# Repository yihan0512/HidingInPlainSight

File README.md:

# This is the code for our Usenix security 2022 paper "Hiding in Plain Sight? On the Efficacy of Power Side Channel-Based Control Flow Monitoring"

## Our paper can be found here.

## installation
- install anaconda3
- create a conda virtual environment: `conda create --prefix ./environment python=3.8`
- install pytorch: follow instructions on pytorch.org to install the pytorch version that fits your cuda version
- install hmmlearn: `pip install hmmlearn`
- install our customized chipwhisperer (in `chipwhisperer/`): `python -m pip install -e . --user`

## how to use
please check the readme file in each subdirectory for detailed steps for each program

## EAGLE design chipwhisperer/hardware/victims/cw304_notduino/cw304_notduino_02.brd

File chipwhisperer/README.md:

# ChipWhisperer

[Wiki](https://wiki.newae.com/V5:Main_Page) |[Documentation](https://chipwhisperer.readthedocs.io) |[Knowledge Base](https://wiki.newae.com/Category:Knowledge_Base) | [Forum](http://www.newae.com/forum) | [Store](https://store.newae.com) | [NewAE](http://newae.com)

ChipWhisperer is an open source toolchain dedicated to hardware security research. This toolchain consists of several layers of open source components:
* __Hardware__: The ChipWhisperer uses a _capture_ board and a _target_ board. Schematics and PCB layouts for the ChipWhisperer-Lite capture board and a number of target boards are freely available.
* __Firmware__: Three separate pieces of firmware are used on the ChipWhisperer hardware. The capture board has a USB controller (in C) and an FPGA for high-speed captures (in Verilog) with open-source firmware. Also, the target device has its own firmware; this repository includes many firmware examples for different targets.
* __Software__: The ChipWhisperer software is made up of a _capture_ program to control the hardware and an _analyzer_ program to process captured data.

---

## ChipWhisperer 5.0 Is Here

The biggest (and most breaking) change is here. ChipWhisperer 5.0 uses Python 3 & Juypter Notebooks. Here is a brief summary of improvements:

* Uses Jupyter Notebooks
* Python 3 
* Fully documented API (finally)
* 19 Jupyter notebook tutorials for side-channel analysis with ChipWhisperer
* 5x improved capture speed
* Tutorials all include output with three different targets (Nano, Lite (XMEGA), Lite (STM32F)), making it easier to compare your output to the tutorials output when you are following along.
* Fully usable as a standalone python package
* Project API supports import and export to zip file to move projects around.

An overview of the major changes can be found on the new ReadtheDocs [Overview Page](https://chipwhisperer.readthedocs.io/en/stable/getting-started.html).

We highly recommend you switch to CW5 as all development since last year has been for CW5, and will continue this way. The final tagged version of CW4 is 4.0.5, it can be found in the **develop** branch if you insist. 

## Getting Started
First time using ChipWhisperer? Check out these links:
* [Getting Started](https://wiki.newae.com/V5:Getting_Started) if you have no idea where to start
* [CW5 Information](https://wiki.newae.com/CW5) for information about ChipWhisperer 5 and Jupyter.
* [Installing ChipWhisperer](https://chipwhisperer.readthedocs.io/en/latest/installing.html) if you're trying to set up this software package

## GIT Source
Note all development occurs on the [develop](https://github.com/newaetech/chipwhisperer/tree/develop) branch. If you are looking for bleeding edge it's NOT on master - we push each release (and possibly any critical changes) to master. This means that "master" always gives you the latest known-working branch, but there may be new features on the "develop" branch.

## Help!
Stuck? If you need a hand, there are a few places you can ask for help:
* The [NewAE Forum](https://www.newae.com/forum/) is full of helpful people that can point you in the right direction
* If you find a bug, let us know through the [issue tracker](https://github.com/newaetech/chipwhisperer/issues)

---

ChipWhisperer is a trademark of NewAE Technology Inc., registered in the US, Europe, and China.

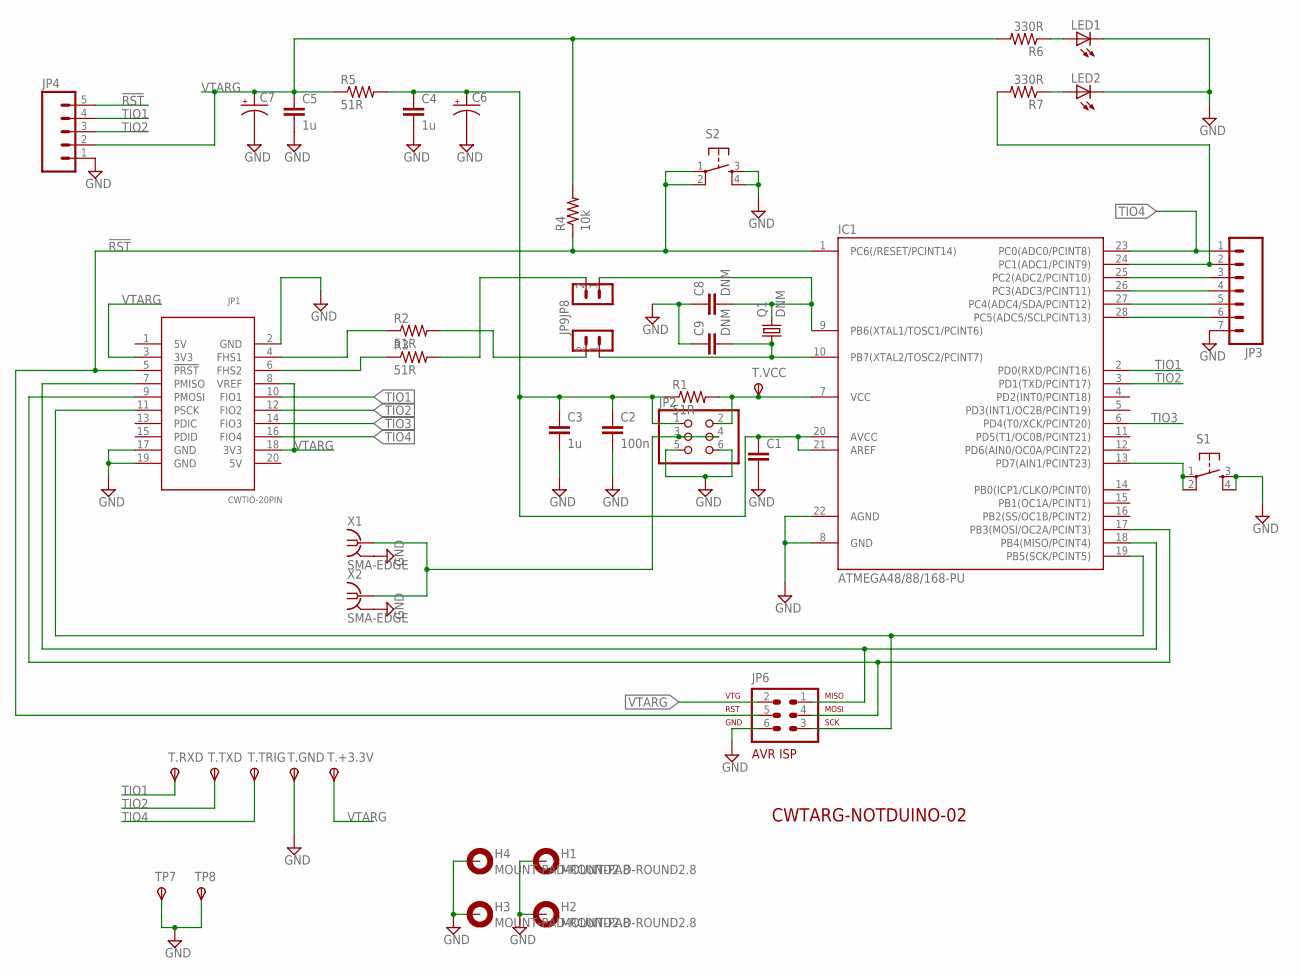
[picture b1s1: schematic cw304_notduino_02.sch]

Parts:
C1: CAPPTH; CAP-PTH-SMALL
C2: 100n; CAP-PTH-SMALL
C3, C4, C5: 1u; CAP-PTH-SMALL
C6, C7: CAP_POLPTH1; CPOL-RADIAL-100UF-25V
C8, C9: DNM; CAP-PTH-SMALL
H1, H2, H3, H4: MOUNT-PAD-ROUND2.8; 2,8-PAD
IC1: ATMEGA48/88/168-PU; DIL28-3
JP1: CWTIO-20PIN; PINSHRD_PTH_2X10
JP2: PINHD-2X3; 2X03
JP3: M07LOCK; 1X07_LOCK
JP4: M05LOCK; 1X05_LOCK
JP6: AVR-ISP-6
JP8, JP9: M02LOCK; 1X02_LOCK
LED1, LED2: LED5MM
Q1: DNM; HC49U-V
R1, R2, R3, R5: 51R; AXIAL-0.4
R4: 10k; AXIAL-0.4
R6, R7: 330R; AXIAL-0.4
S1, S2: TAC_SWITCHPTH; TACTILE-PTH
T.+3.3V, T.GND, T.RXD, T.TRIG, T.TXD: TPSPAD1-13; P1-13
T.VCC: TPSPAD1-17; P1-17
TP7, TP8: TPSPAD1-17; P1-17
X1, X2: SMA-EDGE; J502-ND-142-0711-821/826

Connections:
!RST: IC1.1 (PC6(/RESET/PCINT14)), JP1.5 (!PRST), JP4.5, JP6.5, R4.P$1 (1), S2.1, S2.2
GND: C1.2, C2.2, C3.2, C4.2, C5.2, C6.2 (-), C7.2 (-), C8.1, C9.1, H1.B2,8, H2.B2,8, H3.B2,8, H4.B2,8, IC1.8 (GND), IC1.22 (AGND), JP1.2 (GND), JP1.17 (GND), JP1.19 (GND), JP2.5, JP2.6, JP3.7, JP4.1, JP6.6, LED1.K (C), LED2.K (C), S1.3, S1.4, S2.3, S2.4, T.GND.TP, TP7.TP, TP8.TP, X1.G@1 (2), X1.G@2 (2), X1.G@3 (2), X1.G@4 (2), X2.G@1 (2), X2.G@2 (2), X2.G@3 (2), X2.G@4 (2)
unnamed: LED2.A, R7.P$1 (1)
unnamed: IC1.18 (PB4(MISO/PCINT4)), JP1.7 (PMISO), JP6.1
unnamed: IC1.17 (PB3(MOSI/OC2A/PCINT3)), JP1.9 (PMOSI), JP6.4
unnamed: JP1.4 (FHS1), R2.P$1 (1)
unnamed: JP1.6 (FHS2), R3.P$1 (1)
unnamed: IC1.19 (PB5(SCK/PCINT5)), JP1.11 (PSCK), JP6.3
unnamed: IC1.7 (VCC), JP2.2, R1.P$2 (2), T.VCC.TP
unnamed: LED1.A, R6.P$1 (1)
unnamed: C1.1, C2.1, C3.1, C4.1, C6.1 (+), IC1.20 (AVCC), IC1.21 (AREF), JP2.1, R1.P$1 (1), R5.P$2 (2)
unnamed: C8.2, IC1.9 (PB6(XTAL1/TOSC1/PCINT6)), JP8.1, Q1.2
unnamed: IC1.13 (PD7(AIN1/PCINT23)), S1.1, S1.2
unnamed: IC1.24 (PC1(ADC1/PCINT9)), JP3.2, R7.P$2 (2)
unnamed: IC1.25 (PC2(ADC2/PCINT10)), JP3.3
unnamed: IC1.26 (PC3(ADC3/PCINT11)), JP3.4
unnamed: IC1.27 (PC4(ADC4/SDA/PCINT12)), JP3.5
unnamed: IC1.28 (PC5(ADC5/SCLPCINT13)), JP3.6
unnamed: JP2.3, JP2.4, X1.1, X2.1
unnamed: C9.2, IC1.10 (PB7(XTAL2/TOSC2/PCINT7)), JP9.1, Q1.1
THS1: JP9.2, R2.P$2 (2)
THS2: JP8.2, R3.P$2 (2)
TIO1: IC1.2 (PD0(RXD/PCINT16)), JP1.10 (FIO1), JP4.4, T.RXD.TP
TIO2: IC1.3 (PD1(TXD/PCINT17)), JP1.12 (FIO2), JP4.3, T.TXD.TP
TIO3: IC1.6 (PD4(T0/XCK/PCINT20)), JP1.14 (FIO3)
TIO4: IC1.23 (PC0(ADC0/PCINT8)), JP1.16 (FIO4), JP3.1, T.TRIG.TP
VTARG: C5.1, C7.1 (+), JP1.3 (3V3), JP1.8 (VREF), JP1.18 (3V3), JP4.2, JP6.2, R4.P$2 (2), R5.P$1 (1), R6.P$2 (2), T.+3.3V.TP

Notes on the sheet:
CWTARG-NOTDUINO-02

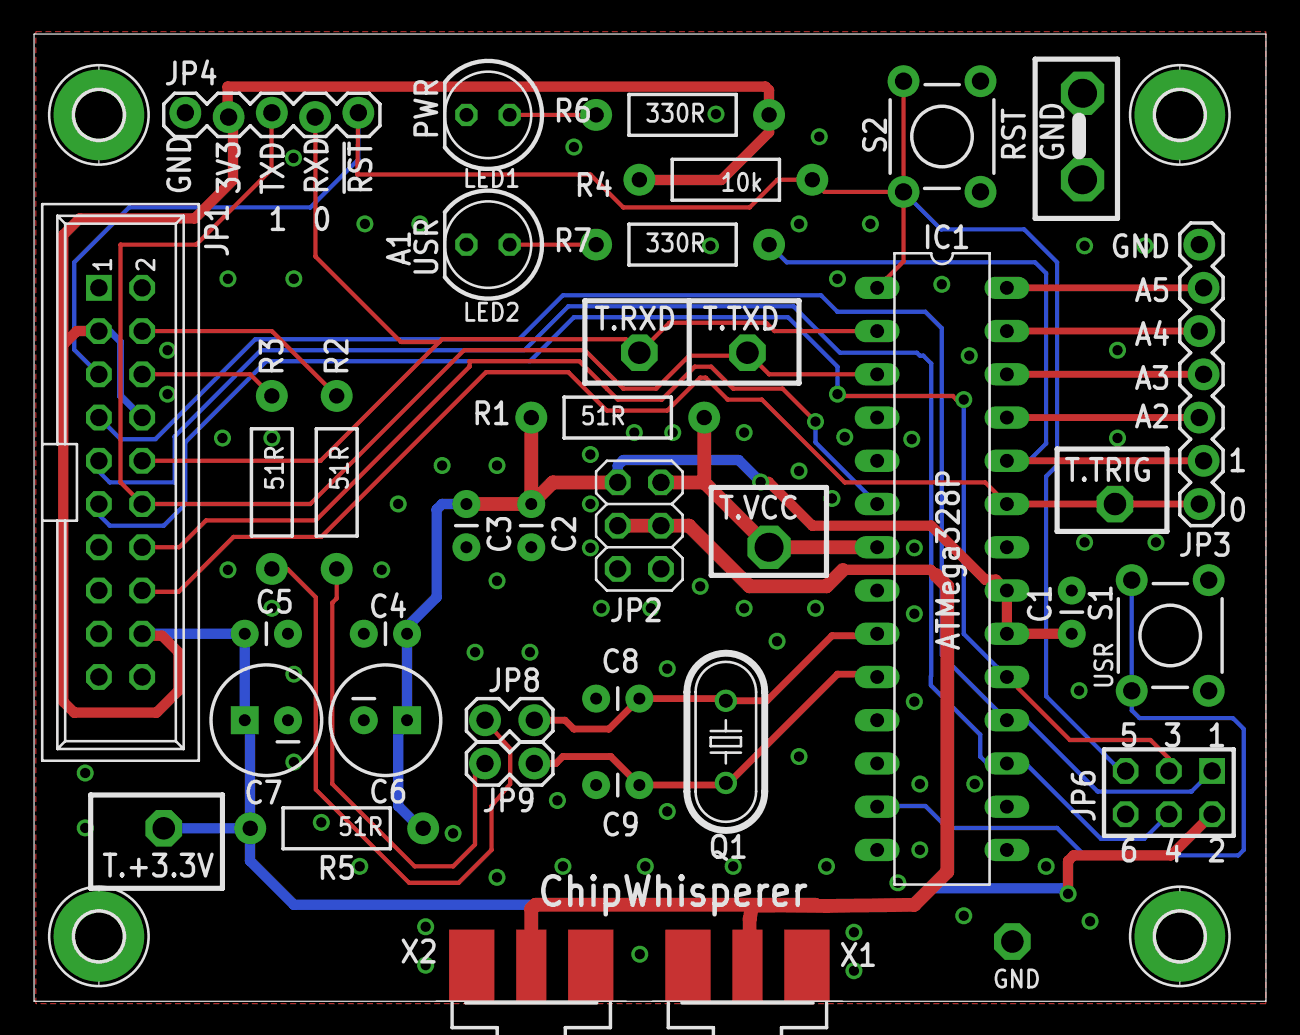
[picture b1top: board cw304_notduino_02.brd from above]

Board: 2 copper layers, 72.4 x 56.8 mm, 43 parts (0 on the bottom side), 27 nets.

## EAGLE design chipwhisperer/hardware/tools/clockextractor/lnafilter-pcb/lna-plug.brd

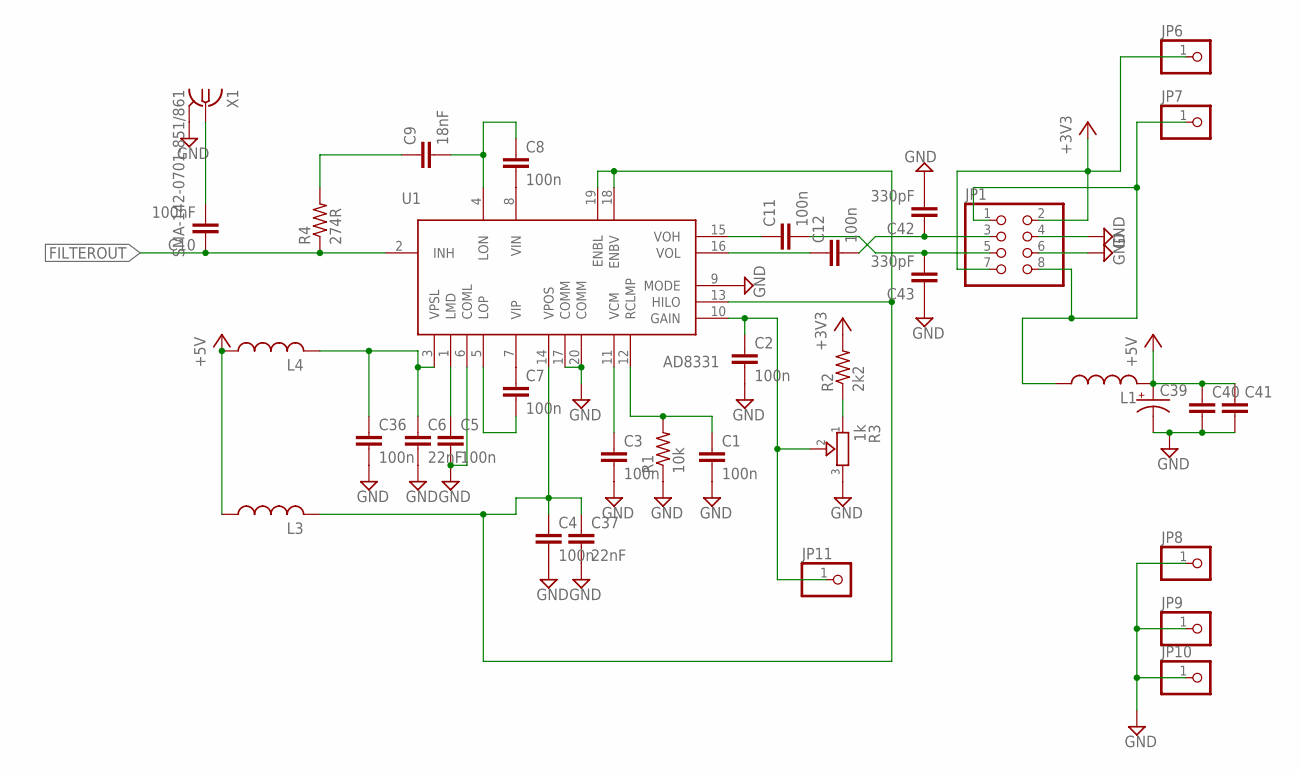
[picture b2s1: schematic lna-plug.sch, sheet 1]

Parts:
C1, C2, C3, C4, C5, C7, C8, C11, C12, C36: 100n; C0603
C6, C37: 22nF; C0603
C9: 18nF; C0603
C10: 100nF; C0603
C39: CPOL-USSMCC; SMC_C
C40: C-EUC1206; C1206
C41: C-EUC0805; C0805
C42, C43: 330pF; C0603
JP1: PINHD-2X4; 2X04
JP6, JP7, JP8, JP9, JP10, JP11: PINHD-1X1; 1X01
L1, L3, L4: L-USL2012C; L2012C
R1: 10k; R0603
R2: 2k2; R0603
R3: 1k; TRIMMER_3362P
R4: 274R; R0603
U1: AD8331; QSOP20
X1: SMA-142-0701-851/861; J502-ND-142-0701-851/861

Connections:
+3V3: JP1.2, JP1.7, JP6.1, R2.2; also elsewhere on the board
+5V: C39.+, C40.1, C41.1, L1.2, L3.1, L4.1
FILTEROUT: C10.1, R4.1, U1.2 (INH); also elsewhere on the board
GND: C1.2, C2.2, C3.2, C4.2, C5.2, C6.2, C36.2, C37.2, C39.-, C40.2, C41.2, C42.2, C43.1, JP1.4, JP1.6, JP8.1, JP9.1, JP10.1, R1.1, R3.3, U1.6 (COML), U1.9 (MODE), U1.17 (COMM), U1.20 (COMM), X1.G@1 (2), X1.G@2 (2), X1.G@3 (2), X1.G@4 (2); also elsewhere on the board
unnamed: C7.1, U1.7 (VIP)
unnamed: C8.2, U1.8 (VIN)
unnamed: C8.1, C9.2, U1.4 (LON)
unnamed: C7.2, U1.5 (LOP)
unnamed: C3.1, U1.11 (VCM)
unnamed: C1.1, R1.2, U1.12 (RCLMP)
unnamed: C2.1, JP11.1, R3.2, U1.10 (GAIN)
unnamed: R2.1, R3.1
unnamed: C5.1, U1.1 (LMD)
unnamed: C6.1, C36.1, L4.2, U1.3 (VPSL)
unnamed: C9.1, R4.2
unnamed: C12.1, U1.16 (VOL)
unnamed: C11.1, U1.15 (VOH)
unnamed: C12.2, C42.1, JP1.3
unnamed: C11.2, C43.2, JP1.5
unnamed: JP1.1, JP1.8, JP7.1, L1.1
unnamed: C10.2, X1.1
unnamed: C4.1, C37.1, L3.2, U1.13 (HILO), U1.14 (VPOS), U1.18 (ENBV), U1.19 (ENBL)

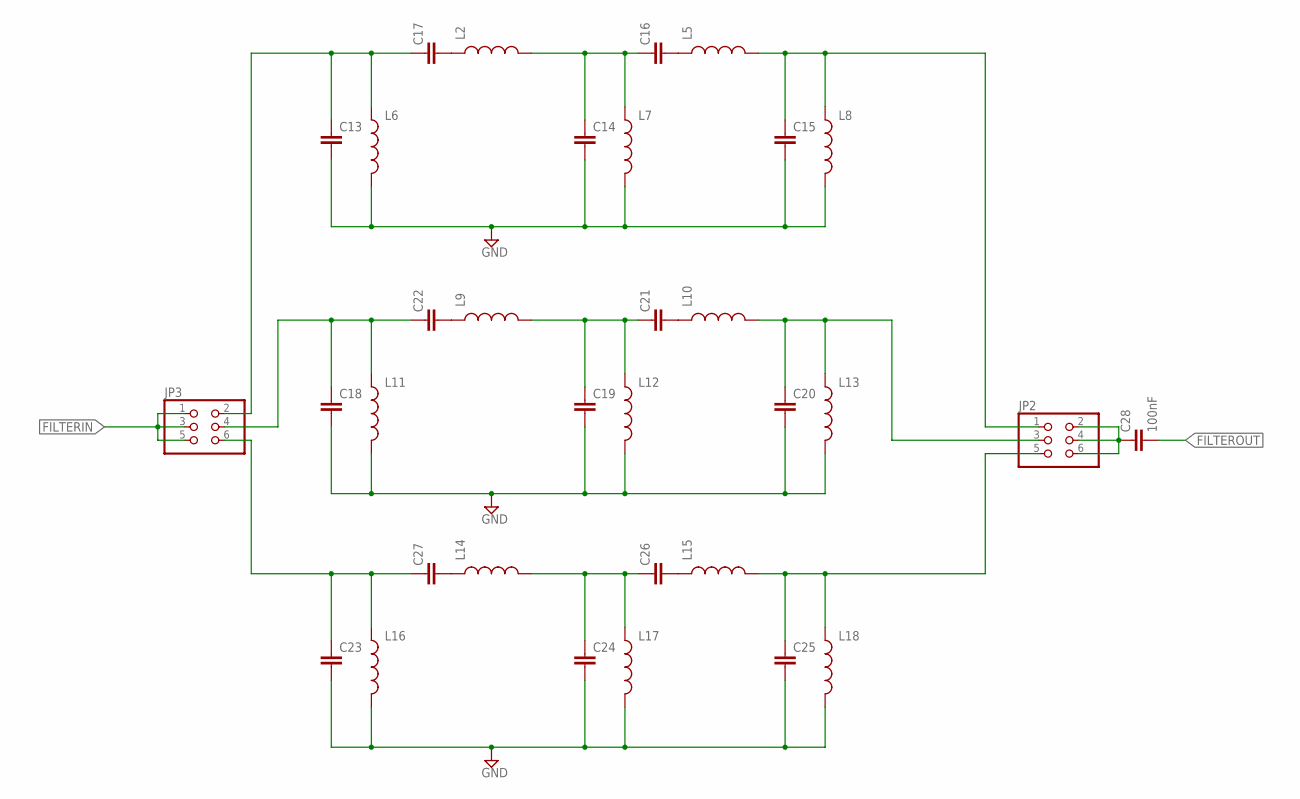
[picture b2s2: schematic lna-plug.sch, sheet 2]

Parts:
C13, C14, C15, C16, C17, C18, C19, C20, C21, C22, C23, C24, C25, C26, C27: C-EUC0603; C0603
C28: 100nF; C0603
JP2, JP3: PINHD-2X3; 2X03
L2, L5, L6, L7, L8, L9, L10, L11, L12, L13, L14, L15, L16, L17, L18: INDUCTOR0603; 0603

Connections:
FILTERIN: JP3.1, JP3.3, JP3.5; also elsewhere on the board
FILTEROUT: C28.2; also elsewhere on the board
GND: C13.2, C14.2, C15.2, C18.2, C19.2, C20.2, C23.2, C24.2, C25.2, L6.2, L7.2, L8.2, L11.2, L12.2, L13.2, L16.2, L17.2, L18.2; also elsewhere on the board
unnamed: C17.2, L2.1
unnamed: C16.2, L5.1
unnamed: C14.1, C16.1, L2.2, L7.1
unnamed: C15.1, JP2.1, L5.2, L8.1
unnamed: C23.1, C27.1, JP3.6, L16.1
unnamed: C22.2, L9.1
unnamed: C21.2, L10.1
unnamed: C19.1, C21.1, L9.2, L12.1
unnamed: C25.1, JP2.5, L15.2, L18.1
unnamed: C18.1, C22.1, JP3.4, L11.1
unnamed: C27.2, L14.1
unnamed: C26.2, L15.1
unnamed: C24.1, C26.1, L14.2, L17.1
unnamed: C28.1, JP2.2, JP2.4, JP2.6
unnamed: C13.1, C17.1, JP3.2, L6.1
unnamed: C20.1, JP2.3, L10.2, L13.1

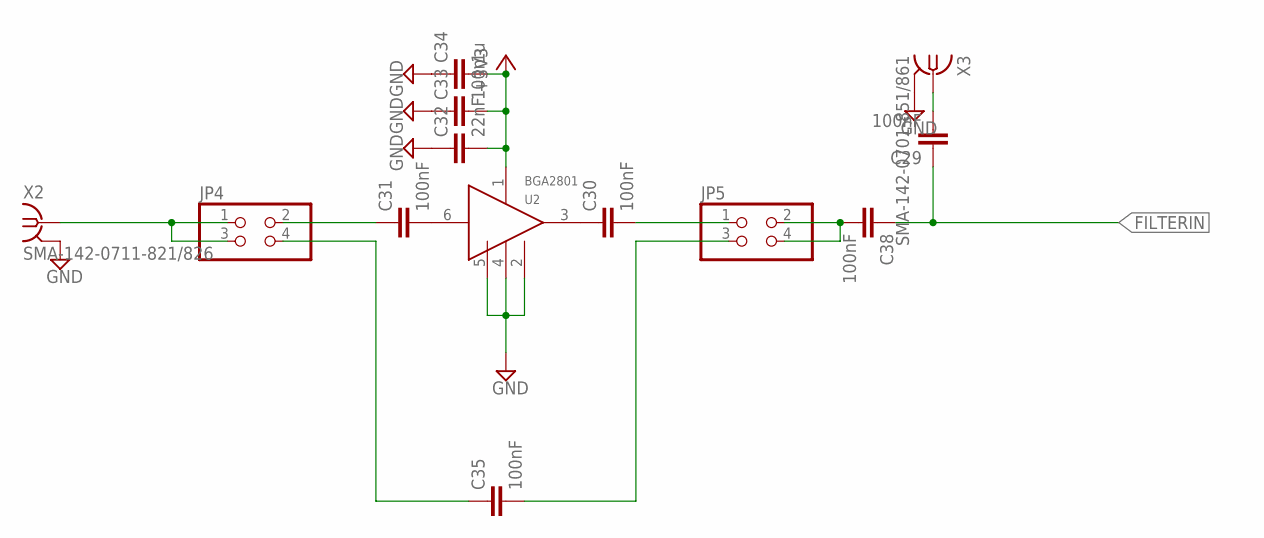
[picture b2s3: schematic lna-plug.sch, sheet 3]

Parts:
C29, C30, C31, C35, C38: 100nF; C0603
C32: 22nF; C0603
C33: 100n; C0603
C34: 1u; C0603
JP4, JP5: PINHD-2X2; 2X02
U2: BGA2801; SOTT323-6
X2: SMA-142-0711-821/826; J502-ND-142-0711-821/826
X3: SMA-142-0701-851/861; J502-ND-142-0701-851/861

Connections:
+3V3: C32.2, C33.2, C34.2, U2.1 (VCC); also elsewhere on the board
FILTERIN: C29.1, C38.1; also elsewhere on the board
GND: C32.1, C33.1, C34.1, U2.2 (GND), U2.4 (GND), U2.5 (GND), X2.G@1 (2), X2.G@2 (2), X2.G@3 (2), X2.G@4 (2), X3.G@1 (2), X3.G@2 (2), X3.G@3 (2), X3.G@4 (2); also elsewhere on the board
unnamed: C38.2, JP5.2, JP5.4
unnamed: C29.2, X3.1
unnamed: C30.1, U2.3 (OUT)
unnamed: C31.2, U2.6 (IN)
unnamed: JP4.1, JP4.3, X2.1
unnamed: C31.1, JP4.2
unnamed: C30.2, JP5.1
unnamed: C35.1, JP4.4
unnamed: C35.2, JP5.3

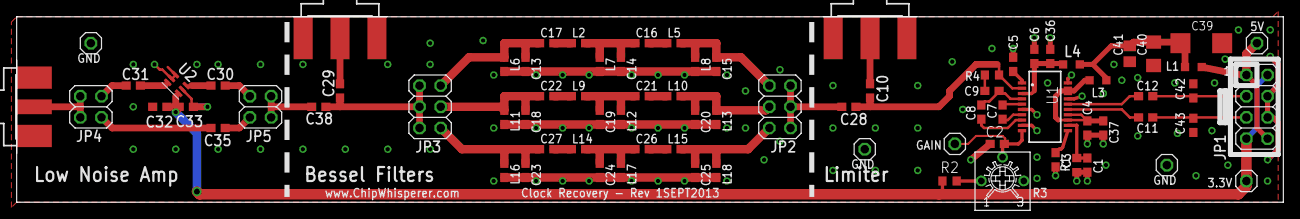
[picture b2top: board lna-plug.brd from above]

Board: 2 copper layers, 151.7 x 22.2 mm, 81 parts (1 on the bottom side), 48 nets.

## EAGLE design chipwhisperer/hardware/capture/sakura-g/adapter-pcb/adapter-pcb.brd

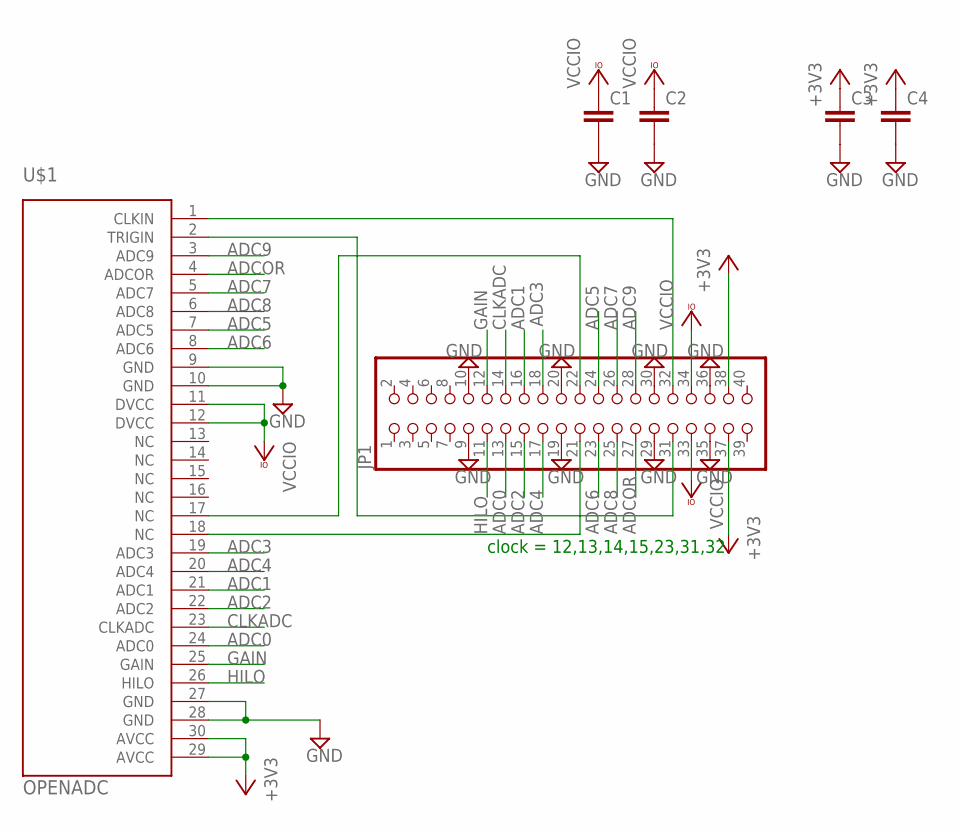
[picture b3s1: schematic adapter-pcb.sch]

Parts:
C1, C2, C3, C4: C-EUC0805; C0805
JP1: PINHD-2X20; 2X20
U$1: OPENADC; OPENADCREV1

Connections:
+3V3: C3.1, C4.1, JP1.37, JP1.38, U$1.29 (AVCC), U$1.30 (AVCC)
ADC0: JP1.13, U$1.24 (ADC0)
ADC1: JP1.16, U$1.21 (ADC1)
ADC2: JP1.15, U$1.22 (ADC2)
ADC3: JP1.18, U$1.19 (ADC3)
ADC4: JP1.17, U$1.20 (ADC4)
ADC5: JP1.24, U$1.7 (ADC5)
ADC6: JP1.23, U$1.8 (ADC6)
ADC7: JP1.26, U$1.5 (ADC7)
ADC8: JP1.25, U$1.6 (ADC8)
ADC9: JP1.28, U$1.3 (ADC9)
ADCOR: JP1.27, U$1.4 (ADCOR)
CLKADC: JP1.14, U$1.23 (CLKADC)
GAIN: JP1.12, U$1.25 (GAIN)
GND: C1.2, C2.2, C3.2, C4.2, JP1.9, JP1.10, JP1.19, JP1.20, JP1.29, JP1.30, JP1.35, JP1.36, U$1.9 (GND), U$1.10 (GND), U$1.27 (GND), U$1.28 (GND)
HILO: JP1.11, U$1.26 (HILO)
unnamed: JP1.32, U$1.1 (CLKIN)
unnamed: JP1.31, U$1.2 (TRIGIN)
unnamed: JP1.21, U$1.18 (NC)
unnamed: JP1.22, U$1.17 (NC)
VCCIO: C1.1, C2.1, JP1.33, JP1.34, U$1.11 (DVCC), U$1.12 (DVCC)

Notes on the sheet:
clock = 12,13,14,15,23,31,32

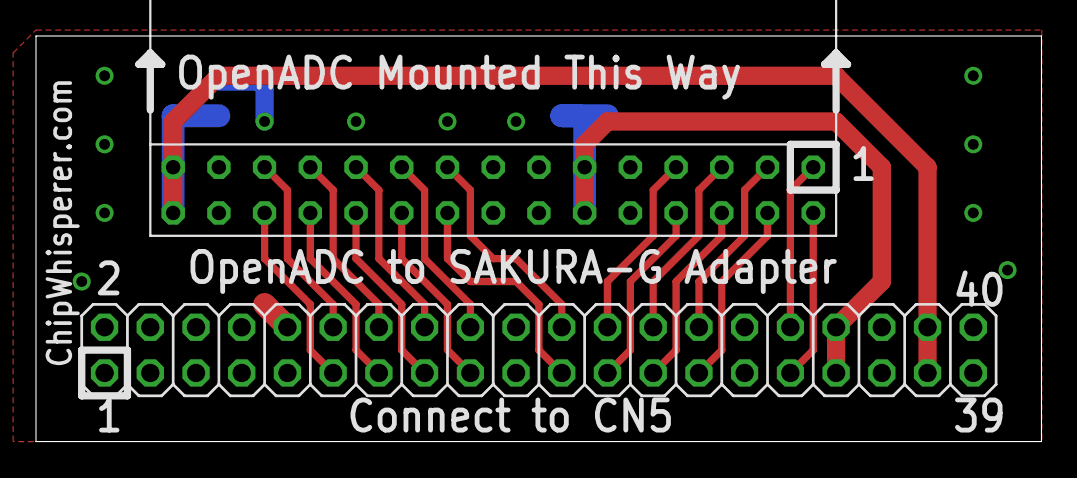
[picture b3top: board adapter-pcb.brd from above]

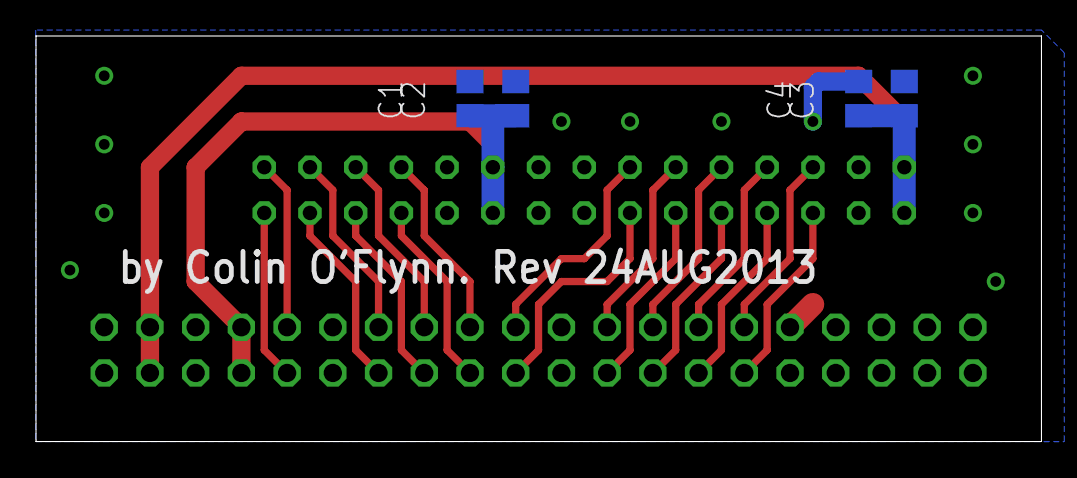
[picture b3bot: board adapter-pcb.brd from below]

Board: 2 copper layers, 55.9 x 22.5 mm, 6 parts (4 on the bottom side), 21 nets.

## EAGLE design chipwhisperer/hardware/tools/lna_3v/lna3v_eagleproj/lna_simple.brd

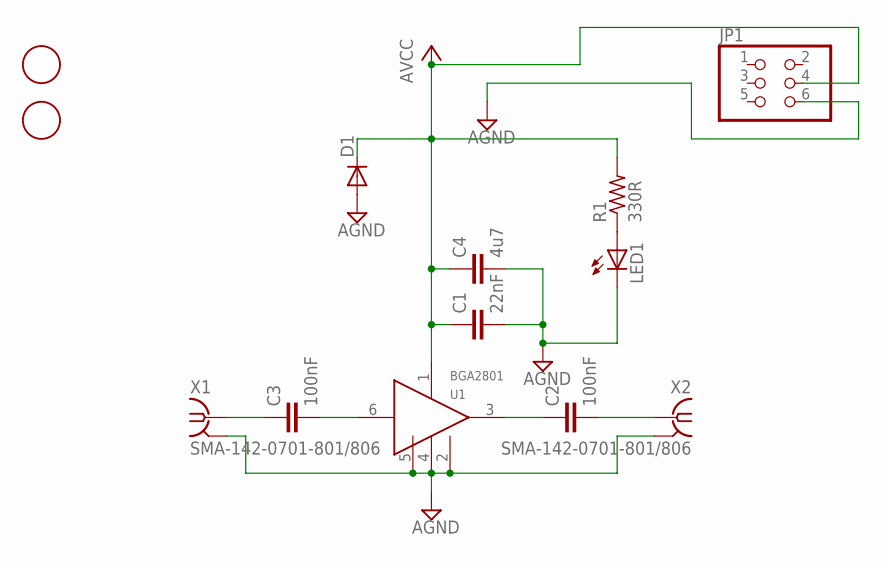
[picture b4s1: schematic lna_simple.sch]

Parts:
C1: 22nF; C0603
C2, C3: 100nF; C0603
C4: 4u7; C0805
D1: DIODE-DO214AC; DO214AC
JP1: PINHD-2X3; 2X03
LED1: LEDCHIP-LED0603; CHIP-LED0603
R1: 330R; R0603
U1: BGA2801; SOTT323-6
U$1, U$2: FIDUCIAL; FIDUCIAL_1MM
X1, X2: SMA-142-0701-801/806; J502-ND-142-0701-801/806

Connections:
AGND: C1.2, C4.2, D1.A, JP1.6, LED1.C, U1.2 (GND), U1.4 (GND), U1.5 (GND), X1.G@1 (2), X1.G@2 (2), X1.G@3 (2), X1.G@4 (2), X2.G@1 (2), X2.G@2 (2), X2.G@3 (2), X2.G@4 (2)
AVCC: C1.1, C4.1, D1.C, JP1.4, R1.2, U1.1 (VCC)
unnamed: C3.2, U1.6 (IN)
unnamed: C2.1, U1.3 (OUT)
unnamed: C2.2, X2.1
unnamed: C3.1, X1.1
unnamed: LED1.A, R1.1

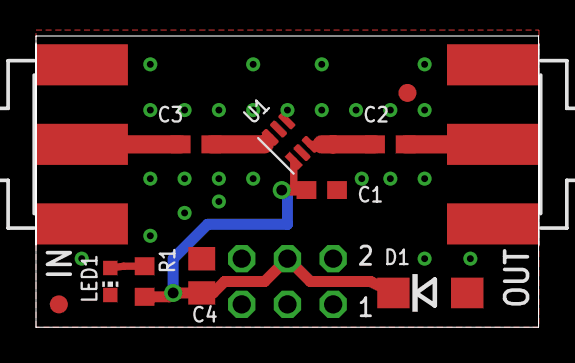
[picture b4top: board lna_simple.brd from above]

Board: 2 copper layers, 27.9 x 16.2 mm, 13 parts (1 on the bottom side), 7 nets.

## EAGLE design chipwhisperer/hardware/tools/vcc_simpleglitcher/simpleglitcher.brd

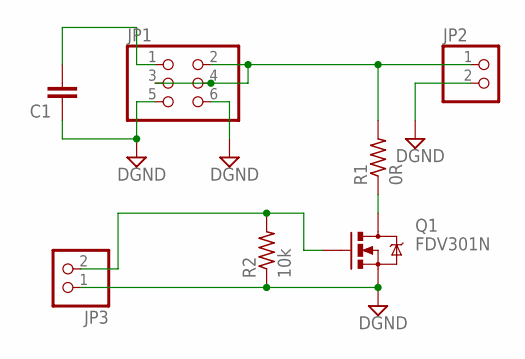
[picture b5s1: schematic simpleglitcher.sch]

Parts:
C1: C-EUC0603; C0603
JP1: PINHD-2X3; 2X03
JP2, JP3: PINHD-1X2; 1X02
Q1: FDV301N; SOT23-3
R1: 0R; R0603
R2: 10k; R0603

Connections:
DGND: C1.1, JP1.5, JP1.6, JP2.2, JP3.1, Q1.2 (S), R2.1
unnamed: JP1.2, JP1.3, JP1.4, JP2.1, R1.2
unnamed: Q1.3 (D), R1.1
unnamed: C1.2, JP1.1
unnamed: JP3.2, Q1.1 (G), R2.2

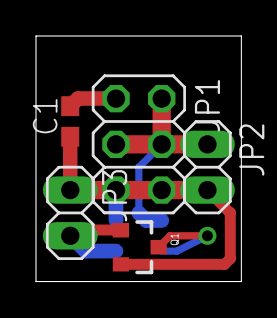
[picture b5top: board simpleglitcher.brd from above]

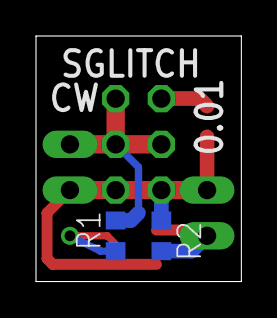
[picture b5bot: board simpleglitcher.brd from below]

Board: 2 copper layers, 11.4 x 13.6 mm, 7 parts (2 on the bottom side), 5 nets.

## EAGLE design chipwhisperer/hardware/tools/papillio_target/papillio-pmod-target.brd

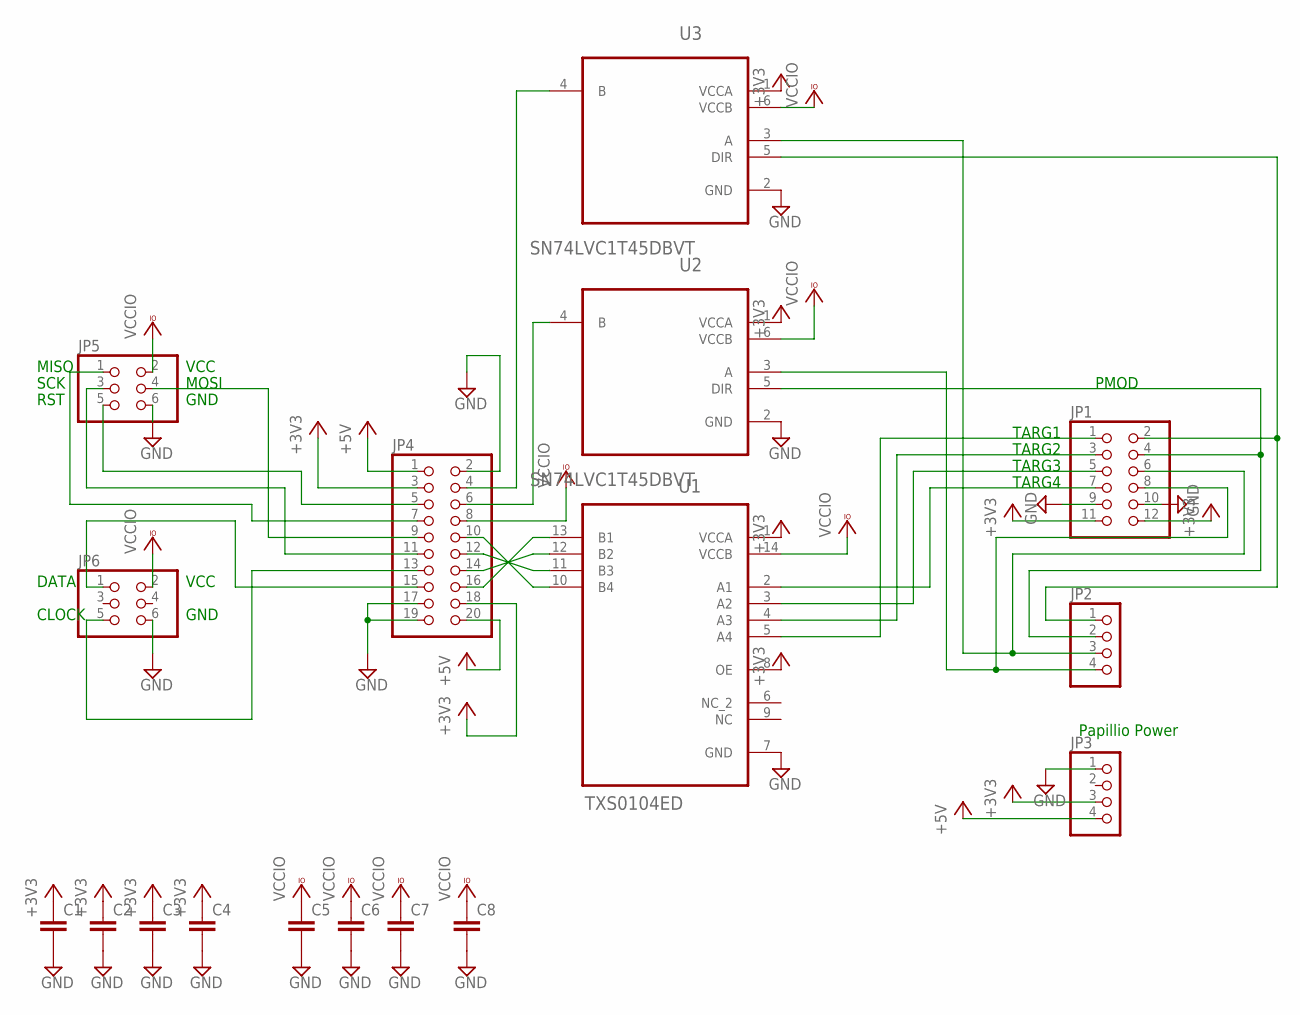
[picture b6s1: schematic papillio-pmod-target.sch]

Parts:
C1, C2, C3, C4, C5, C6, C7, C8: C-EUC0603; C0603
JP1: PINHD-2X6; 2X06
JP2, JP3: PINHD-1X4; 1X04
JP4: PINHD-2X10; 2X10
JP5, JP6: PINHD-2X3; 2X03
U1: TXS0104ED; SOIC127P600X175-14N
U2, U3: SN74LVC1T45DBVT; SOT95P280X145-6N

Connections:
+3V3: C1.1, C2.1, C3.1, C4.1, JP1.11, JP1.12, JP3.3, JP4.3, JP4.18, U1.1 (VCCA), U1.8 (OE), U2.1 (VCCA), U3.1 (VCCA)
+5V: JP3.4, JP4.1, JP4.20
GND: C1.2, C2.2, C3.2, C4.2, C5.2, C6.2, C7.2, C8.2, JP1.9, JP1.10, JP3.1, JP4.2, JP4.17, JP4.19, JP5.6, JP6.6, U1.7 (GND), U2.2 (GND), U3.2 (GND)
unnamed: JP1.2, JP2.1
unnamed: JP1.4, JP2.2, U2.5 (DIR)
unnamed: JP1.6, JP2.3, U3.3 (A)
unnamed: JP1.8, JP2.4, U2.3 (A)
unnamed: JP4.10, U1.10 (B4)
unnamed: JP4.16, U1.13 (B1)
unnamed: JP4.14, U1.12 (B2)
unnamed: JP4.12, U1.11 (B3)
unnamed: JP4.4, U3.4 (B)
unnamed: JP1.1, U1.5 (A4)
unnamed: JP1.3, U1.4 (A3)
unnamed: JP1.5, U1.3 (A2)
unnamed: JP1.7, U1.2 (A1)
unnamed: JP4.6, U2.4 (B)
unnamed: JP4.15, JP6.1
unnamed: JP4.13, JP6.5
unnamed: JP4.5, JP5.5
unnamed: JP4.11, JP5.3
unnamed: JP4.9, JP5.4
unnamed: JP4.7, JP5.1
VCCIO: C5.1, C6.1, C7.1, C8.1, JP4.8, JP5.2, JP6.2, U1.14 (VCCB), U2.6 (VCCB), U3.6 (VCCB)

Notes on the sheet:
PMOD
Papillio Power
TARG1
TARG2
TARG3
TARG4
VCC
MOSI
GND
RST
SCK
MISO
DATA
CLOCK

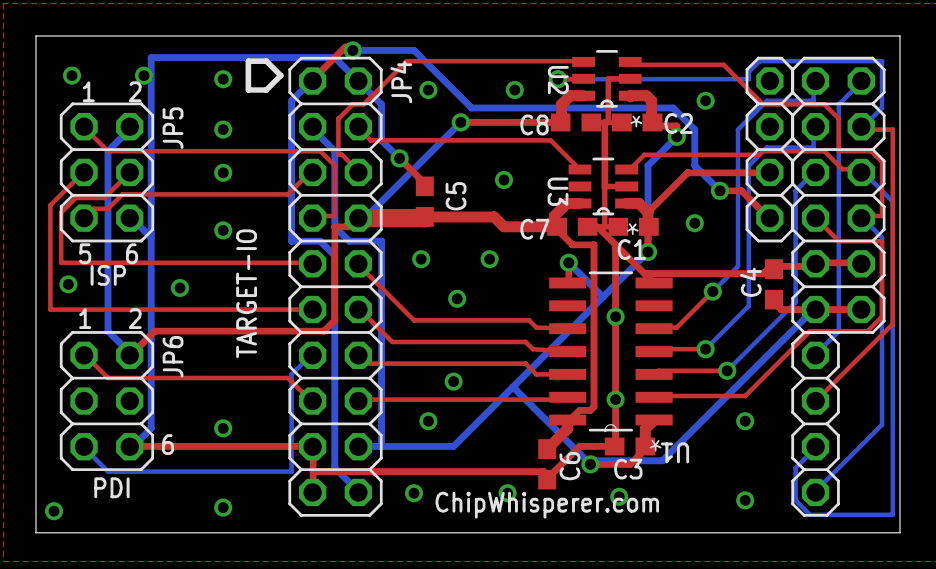
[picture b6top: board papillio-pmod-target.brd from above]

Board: 2 copper layers, 48.0 x 27.6 mm, 17 parts (0 on the bottom side), 24 nets.

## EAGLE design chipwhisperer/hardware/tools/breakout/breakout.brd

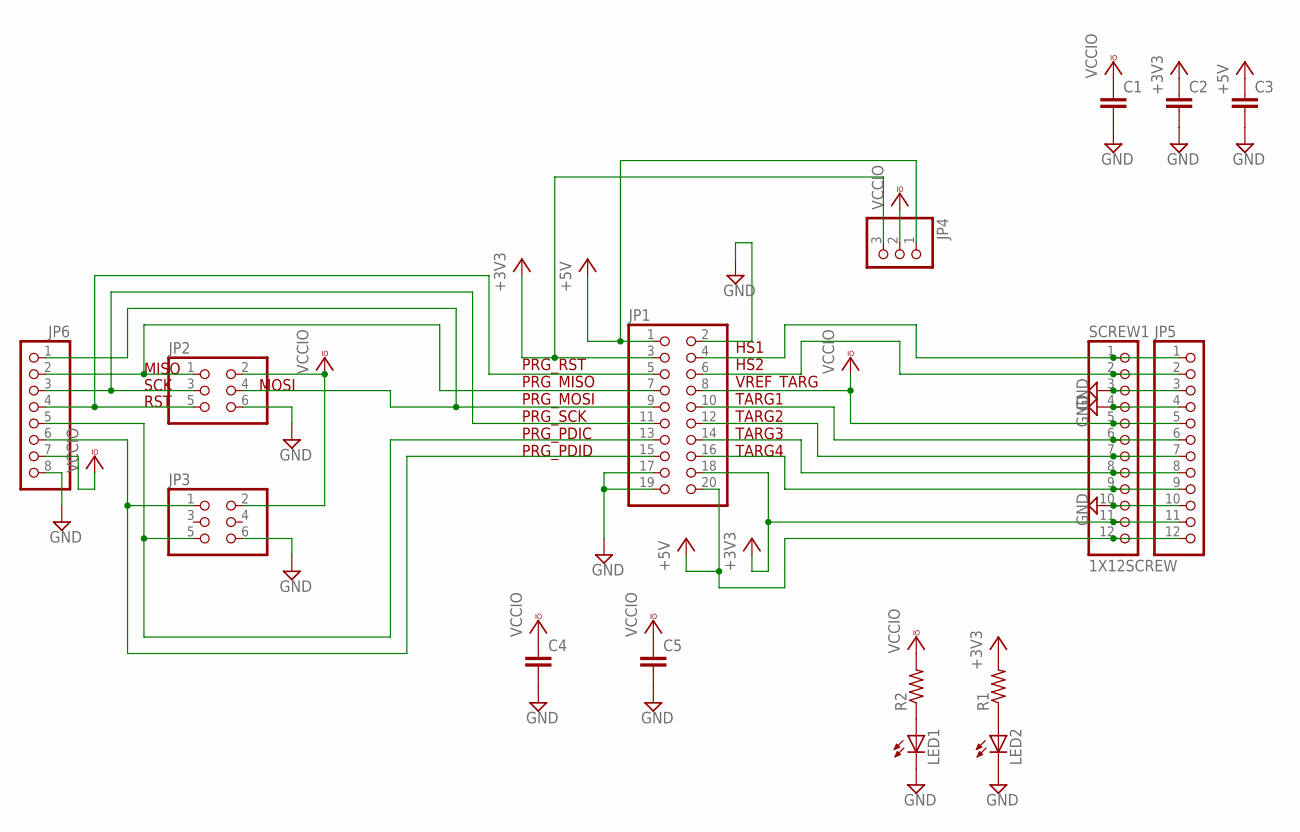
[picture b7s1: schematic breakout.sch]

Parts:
C1, C2, C3, C4, C5: C-EUC0805; C0805
JP1: PINHD-2X10; 2X10
JP2, JP3: PINHD-2X3; 2X03
JP4: PINHD-1X3; 1X03
JP5: PINHD-1X12; 1X12
JP6: PINHD-1X8; 1X08
LED1, LED2: LED3MM
R1, R2: R-US_R0805; R0805
SCREW1: 1X12SCREW; 1X12_SCREW

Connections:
+3V3: C2.1, JP1.3, JP1.18, JP4.3, JP5.11, R1.2, SCREW1.11
+5V: C3.1, JP1.1, JP1.20, JP4.1, JP5.12, SCREW1.12
GND: C1.2, C2.2, C3.2, C4.2, C5.2, JP1.2, JP1.17, JP1.19, JP2.6, JP3.6, JP5.3, JP5.4, JP5.10, JP6.8, LED1.K (C), LED2.K (C), SCREW1.3, SCREW1.4, SCREW1.10
MISO: JP1.7, JP2.1, JP6.2
MOSI: JP1.9, JP2.4, JP6.1
unnamed: LED2.A, R1.1
unnamed: LED1.A, R2.1
unnamed: JP1.4, JP5.1, SCREW1.1
unnamed: JP1.15, JP3.1, JP6.6
unnamed: JP1.13, JP3.5, JP6.5
unnamed: JP1.6, JP5.2, SCREW1.2
unnamed: JP1.10, JP5.6, SCREW1.6
unnamed: JP1.12, JP5.7, SCREW1.7
unnamed: JP1.14, JP5.8, SCREW1.8
unnamed: JP1.16, JP5.9, SCREW1.9
RST: JP1.5, JP2.5, JP6.4
SCK: JP1.11, JP2.3, JP6.3
VCCIO: C1.1, C4.1, C5.1, JP1.8, JP2.2, JP3.2, JP4.2, JP5.5, JP6.7, R2.2, SCREW1.5

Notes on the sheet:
HS1 HS2 VREF_TARG TARG1 TARG2 TARG3 TARG4
PRG_RST PRG_MISO PRG_MOSI PRG_SCK PRG_PDIC PRG_PDID
MISO
SCK
RST
MOSI

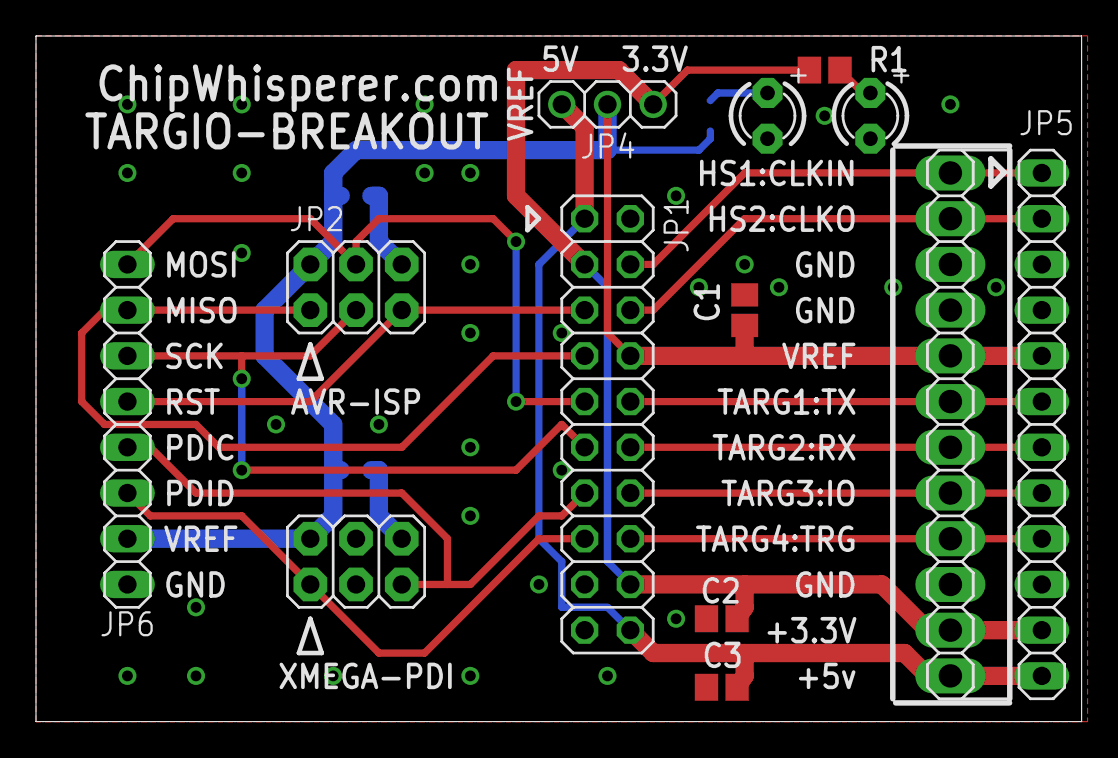
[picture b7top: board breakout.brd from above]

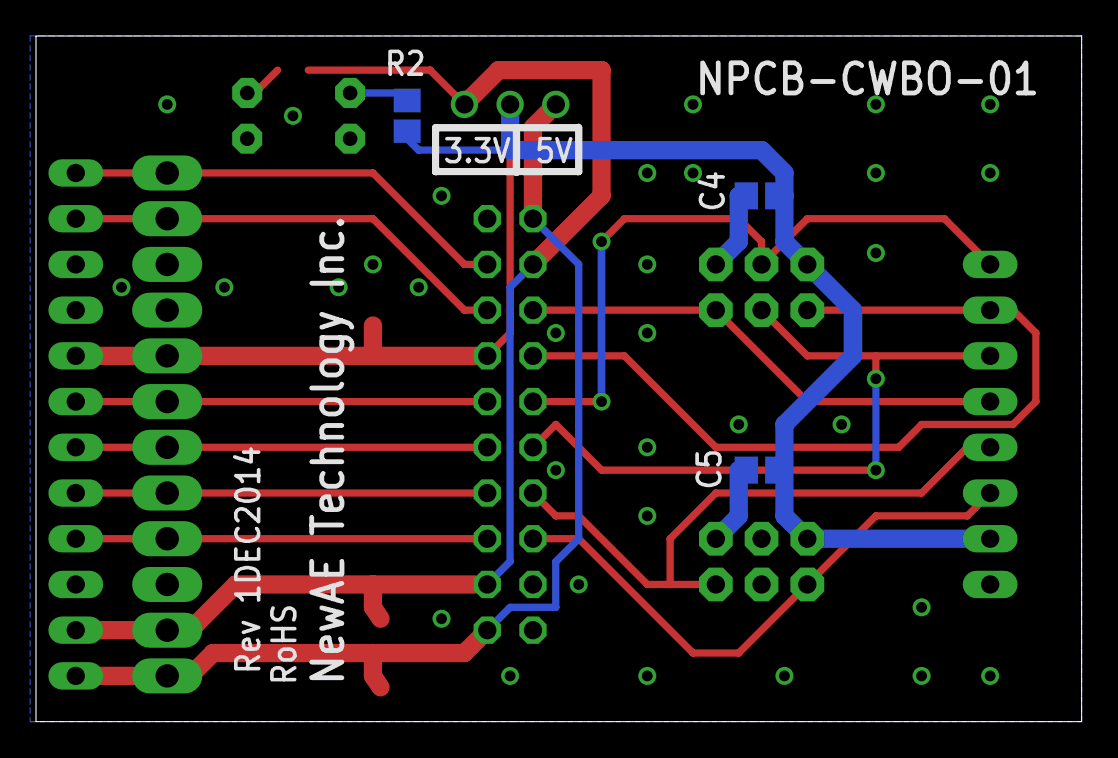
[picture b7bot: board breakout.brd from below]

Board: 2 copper layers, 58.1 x 38.1 mm, 16 parts (3 on the bottom side), 18 nets.

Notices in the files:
chipwhisperer/hardware/victims/cw304_notduino/cw304_notduino_02.brd:
Copyright 2015
parts and their libraries:
SparkFun: Licensing: CC v3.0 Share-Alike You are welcome to use this library for commercial purposes.
